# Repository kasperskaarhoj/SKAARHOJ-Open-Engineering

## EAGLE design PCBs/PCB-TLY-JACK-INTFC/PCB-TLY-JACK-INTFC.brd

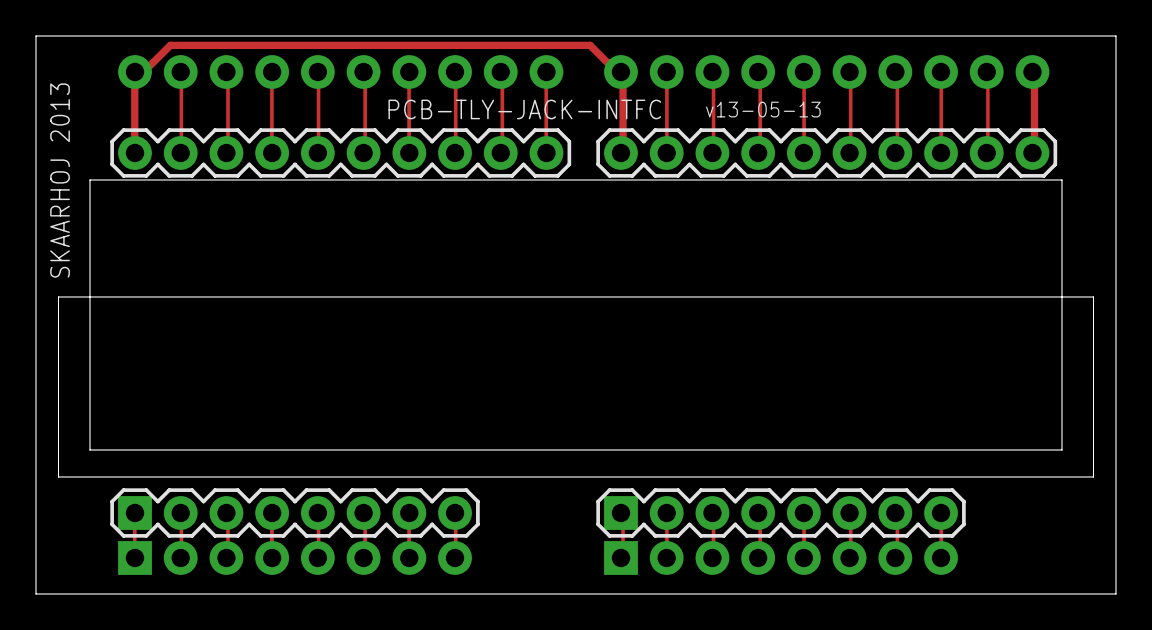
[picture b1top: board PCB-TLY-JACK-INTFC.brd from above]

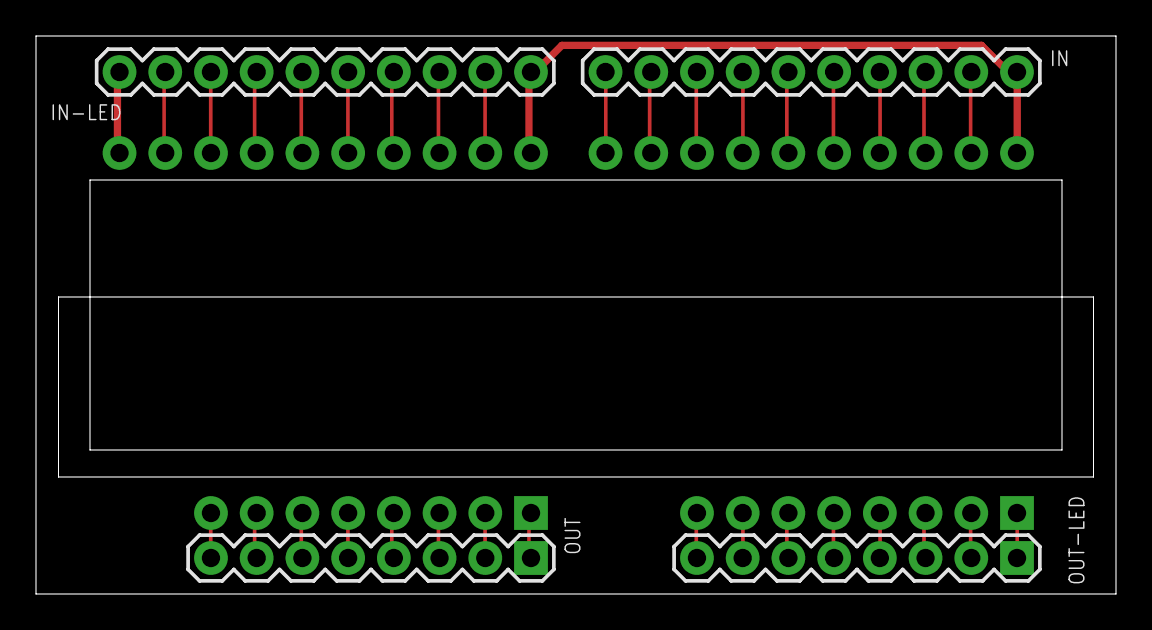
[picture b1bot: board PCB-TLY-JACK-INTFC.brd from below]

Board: 2 copper layers, 60.0 x 31.0 mm, 8 parts (4 on the bottom side), 35 nets.

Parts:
IN, IN1: M10"; 1X10
IN-LED, IN-LED1: M10"; 1X10
OUT, OUT1: 1X08
OUT-LED, OUT-LED1: 1X08

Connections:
5V: IN-LED.10, IN-LED1.10
GND: IN.1, IN1.1, IN-LED.1, IN-LED1.1
IN1: IN-LED.2, IN-LED1.2
IN2: IN-LED.3, IN-LED1.3
IN3: IN-LED.4, IN-LED1.4
IN4: IN-LED.5, IN-LED1.5
IN5: IN-LED.6, IN-LED1.6
IN6: IN-LED.7, IN-LED1.7
IN7: IN-LED.8, IN-LED1.8
IN8: IN-LED.9, IN-LED1.9
unnamed: IN.2, IN1.2
unnamed: IN.3, IN1.3
unnamed: IN.4, IN1.4
unnamed: IN.5, IN1.5
unnamed: IN.6, IN1.6
unnamed: IN.7, IN1.7
unnamed: IN.8, IN1.8
unnamed: IN.9, IN1.9
unnamed: IN.10, IN1.10
unnamed: OUT.8, OUT1.8
unnamed: OUT.7, OUT1.7
unnamed: OUT.6, OUT1.6
unnamed: OUT.5, OUT1.5
unnamed: OUT.4, OUT1.4
unnamed: OUT.3, OUT1.3
unnamed: OUT.2, OUT1.2
unnamed: OUT.1, OUT1.1
O1: OUT-LED.1, OUT-LED1.1
O2: OUT-LED.2, OUT-LED1.2
O3: OUT-LED.3, OUT-LED1.3
O4: OUT-LED.4, OUT-LED1.4
O5: OUT-LED.5, OUT-LED1.5
O6: OUT-LED.6, OUT-LED1.6
O7: OUT-LED.7, OUT-LED1.7
O8: OUT-LED.8, OUT-LED1.8

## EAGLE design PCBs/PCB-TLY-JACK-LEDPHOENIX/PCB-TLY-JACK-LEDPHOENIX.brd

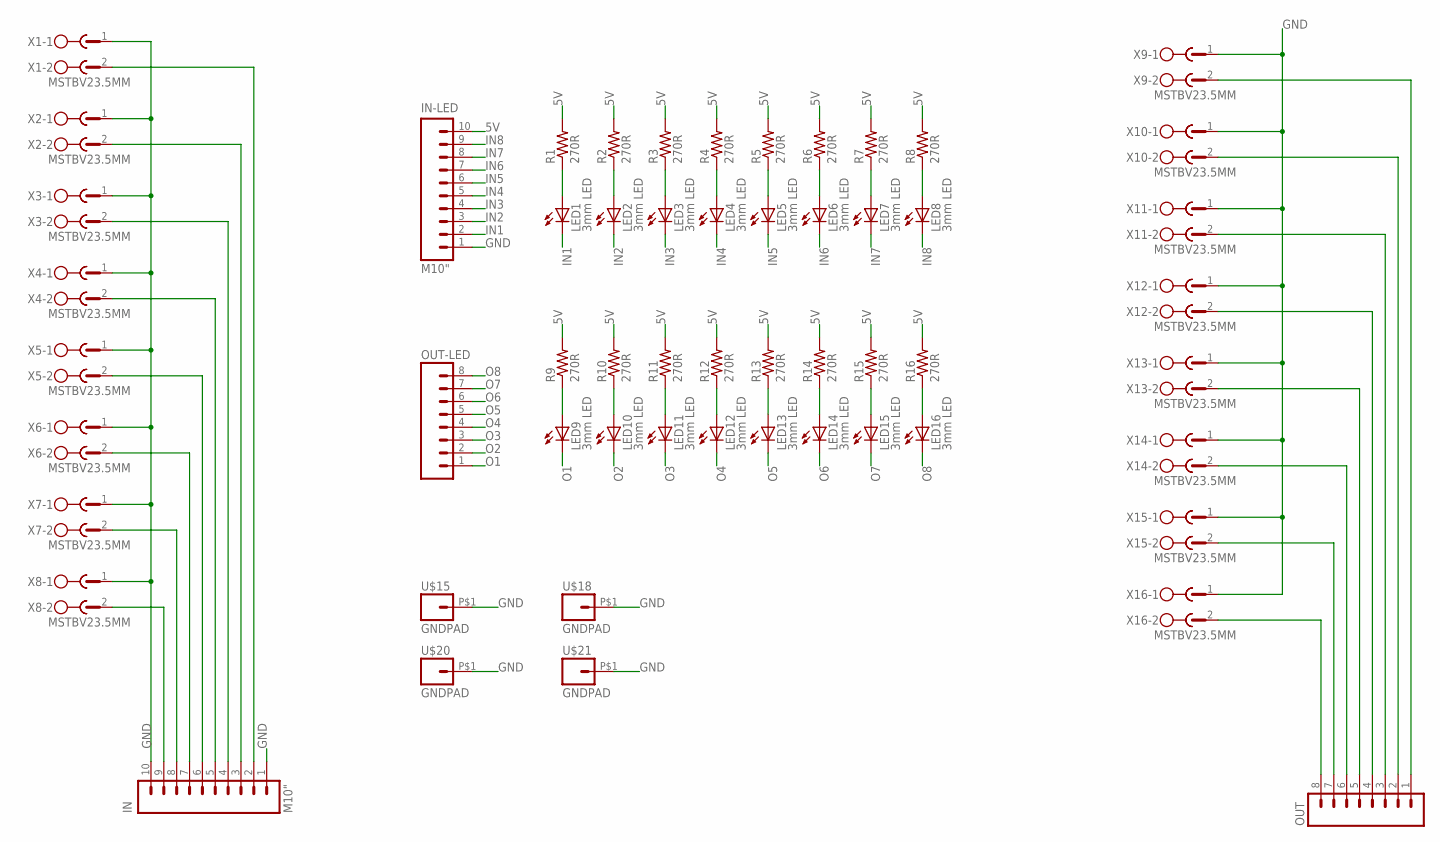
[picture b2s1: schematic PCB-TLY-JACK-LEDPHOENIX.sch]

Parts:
IN: M10"; 1X10
IN-LED: M10"; 1X10
LED1, LED2, LED3, LED4, LED5, LED6, LED7, LED8, LED9, LED10, LED11, LED12, LED13, LED14, LED15, LED16: 3mm LED; LED-1206
OUT: M081X08; 1X08
OUT-LED: M081X08; 1X08
R1, R2, R3, R4, R5, R6, R7, R8, R9, R10, R11, R12, R13, R14, R15, R16: 270R; 0603-RES
U$15, U$18, U$20, U$21: GNDPAD; 3.2MMPAD
X1, X2, X3, X4, X5, X6, X7, X8, X9, X10, X11, X12, X13, X14, X15, X16: MSTBV23.5MM; MSTBV2-3.5

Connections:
5V: IN-LED.10, R1.2, R2.2, R3.2, R4.2, R5.2, R6.2, R7.2, R8.2, R9.2, R10.2, R11.2, R12.2, R13.2, R14.2, R15.2, R16.2
GND: IN.1, IN.10, IN-LED.1, U$15.P$1, U$18.P$1, U$20.P$1, U$21.P$1, X1.1, X2.1, X3.1, X4.1, X5.1, X6.1, X7.1, X8.1, X9.1, X10.1, X11.1, X12.1, X13.1, X14.1, X15.1, X16.1
IN1: IN-LED.2, LED1.C
IN2: IN-LED.3, LED2.C
IN3: IN-LED.4, LED3.C
IN4: IN-LED.5, LED4.C
IN5: IN-LED.6, LED5.C
IN6: IN-LED.7, LED6.C
IN7: IN-LED.8, LED7.C
IN8: IN-LED.9, LED8.C
unnamed: LED1.A, R1.1
unnamed: LED2.A, R2.1
unnamed: LED3.A, R3.1
unnamed: LED4.A, R4.1
unnamed: LED5.A, R5.1
unnamed: LED6.A, R6.1
unnamed: LED7.A, R7.1
unnamed: LED8.A, R8.1
unnamed: LED9.A, R9.1
unnamed: LED10.A, R10.1
unnamed: LED11.A, R11.1
unnamed: LED12.A, R12.1
unnamed: LED13.A, R13.1
unnamed: LED14.A, R14.1
unnamed: LED15.A, R15.1
unnamed: LED16.A, R16.1
unnamed: OUT.2, X10.2
unnamed: OUT.3, X11.2
unnamed: OUT.4, X12.2
unnamed: OUT.5, X13.2
unnamed: OUT.1, X9.2
unnamed: OUT.6, X14.2
unnamed: OUT.7, X15.2
unnamed: OUT.8, X16.2
unnamed: IN.2, X1.2
unnamed: IN.6, X5.2
unnamed: IN.3, X2.2
unnamed: IN.4, X3.2
unnamed: IN.5, X4.2
unnamed: IN.7, X6.2
unnamed: IN.8, X7.2
unnamed: IN.9, X8.2
O1: LED9.C, OUT-LED.1
O2: LED10.C, OUT-LED.2
O3: LED11.C, OUT-LED.3
O4: LED12.C, OUT-LED.4
O5: LED13.C, OUT-LED.5
O6: LED14.C, OUT-LED.6
O7: LED15.C, OUT-LED.7
O8: LED16.C, OUT-LED.8

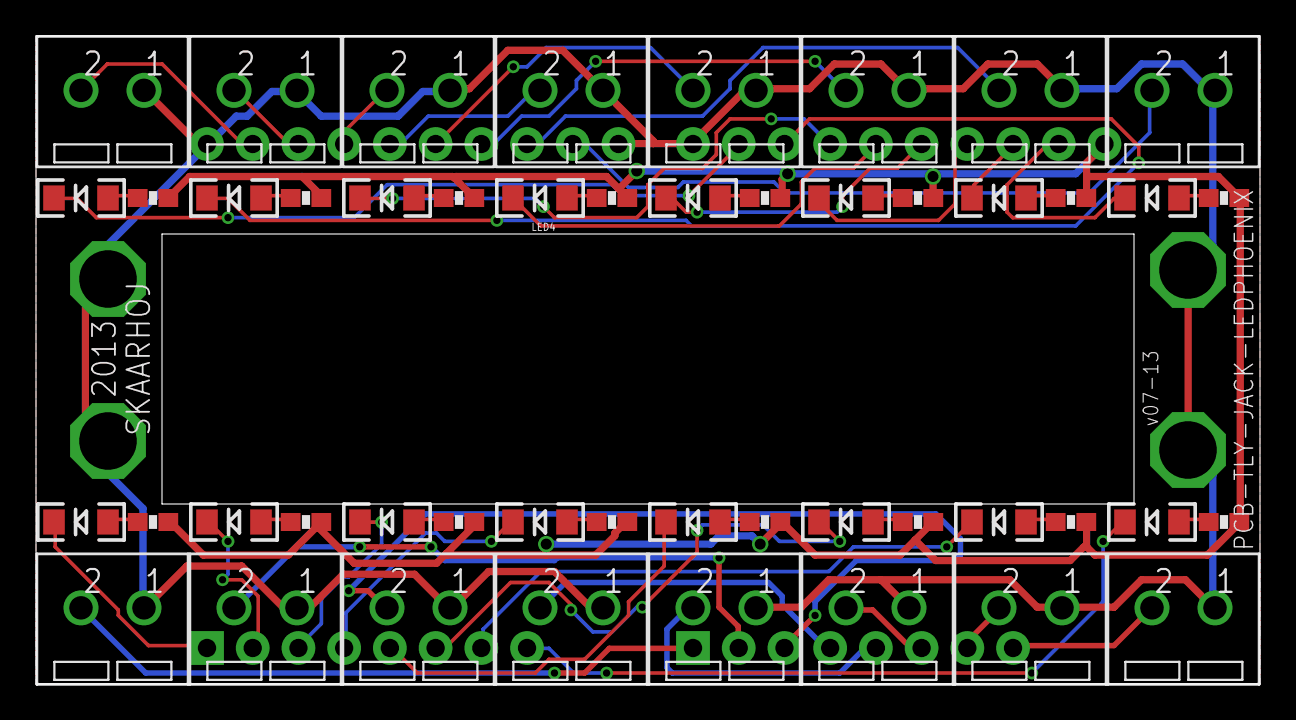
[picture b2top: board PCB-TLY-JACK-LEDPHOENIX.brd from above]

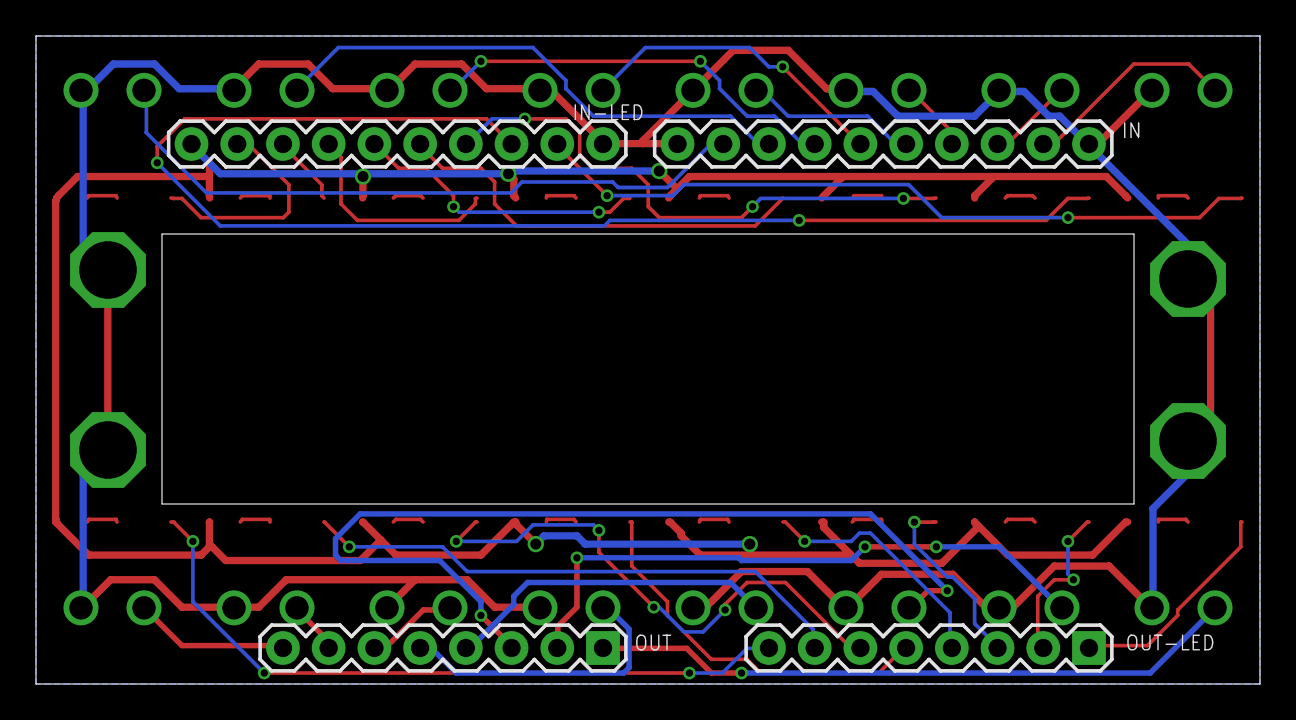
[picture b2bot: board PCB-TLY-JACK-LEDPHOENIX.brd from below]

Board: 2 copper layers, 68.0 x 36.0 mm, 56 parts (4 on the bottom side), 50 nets.

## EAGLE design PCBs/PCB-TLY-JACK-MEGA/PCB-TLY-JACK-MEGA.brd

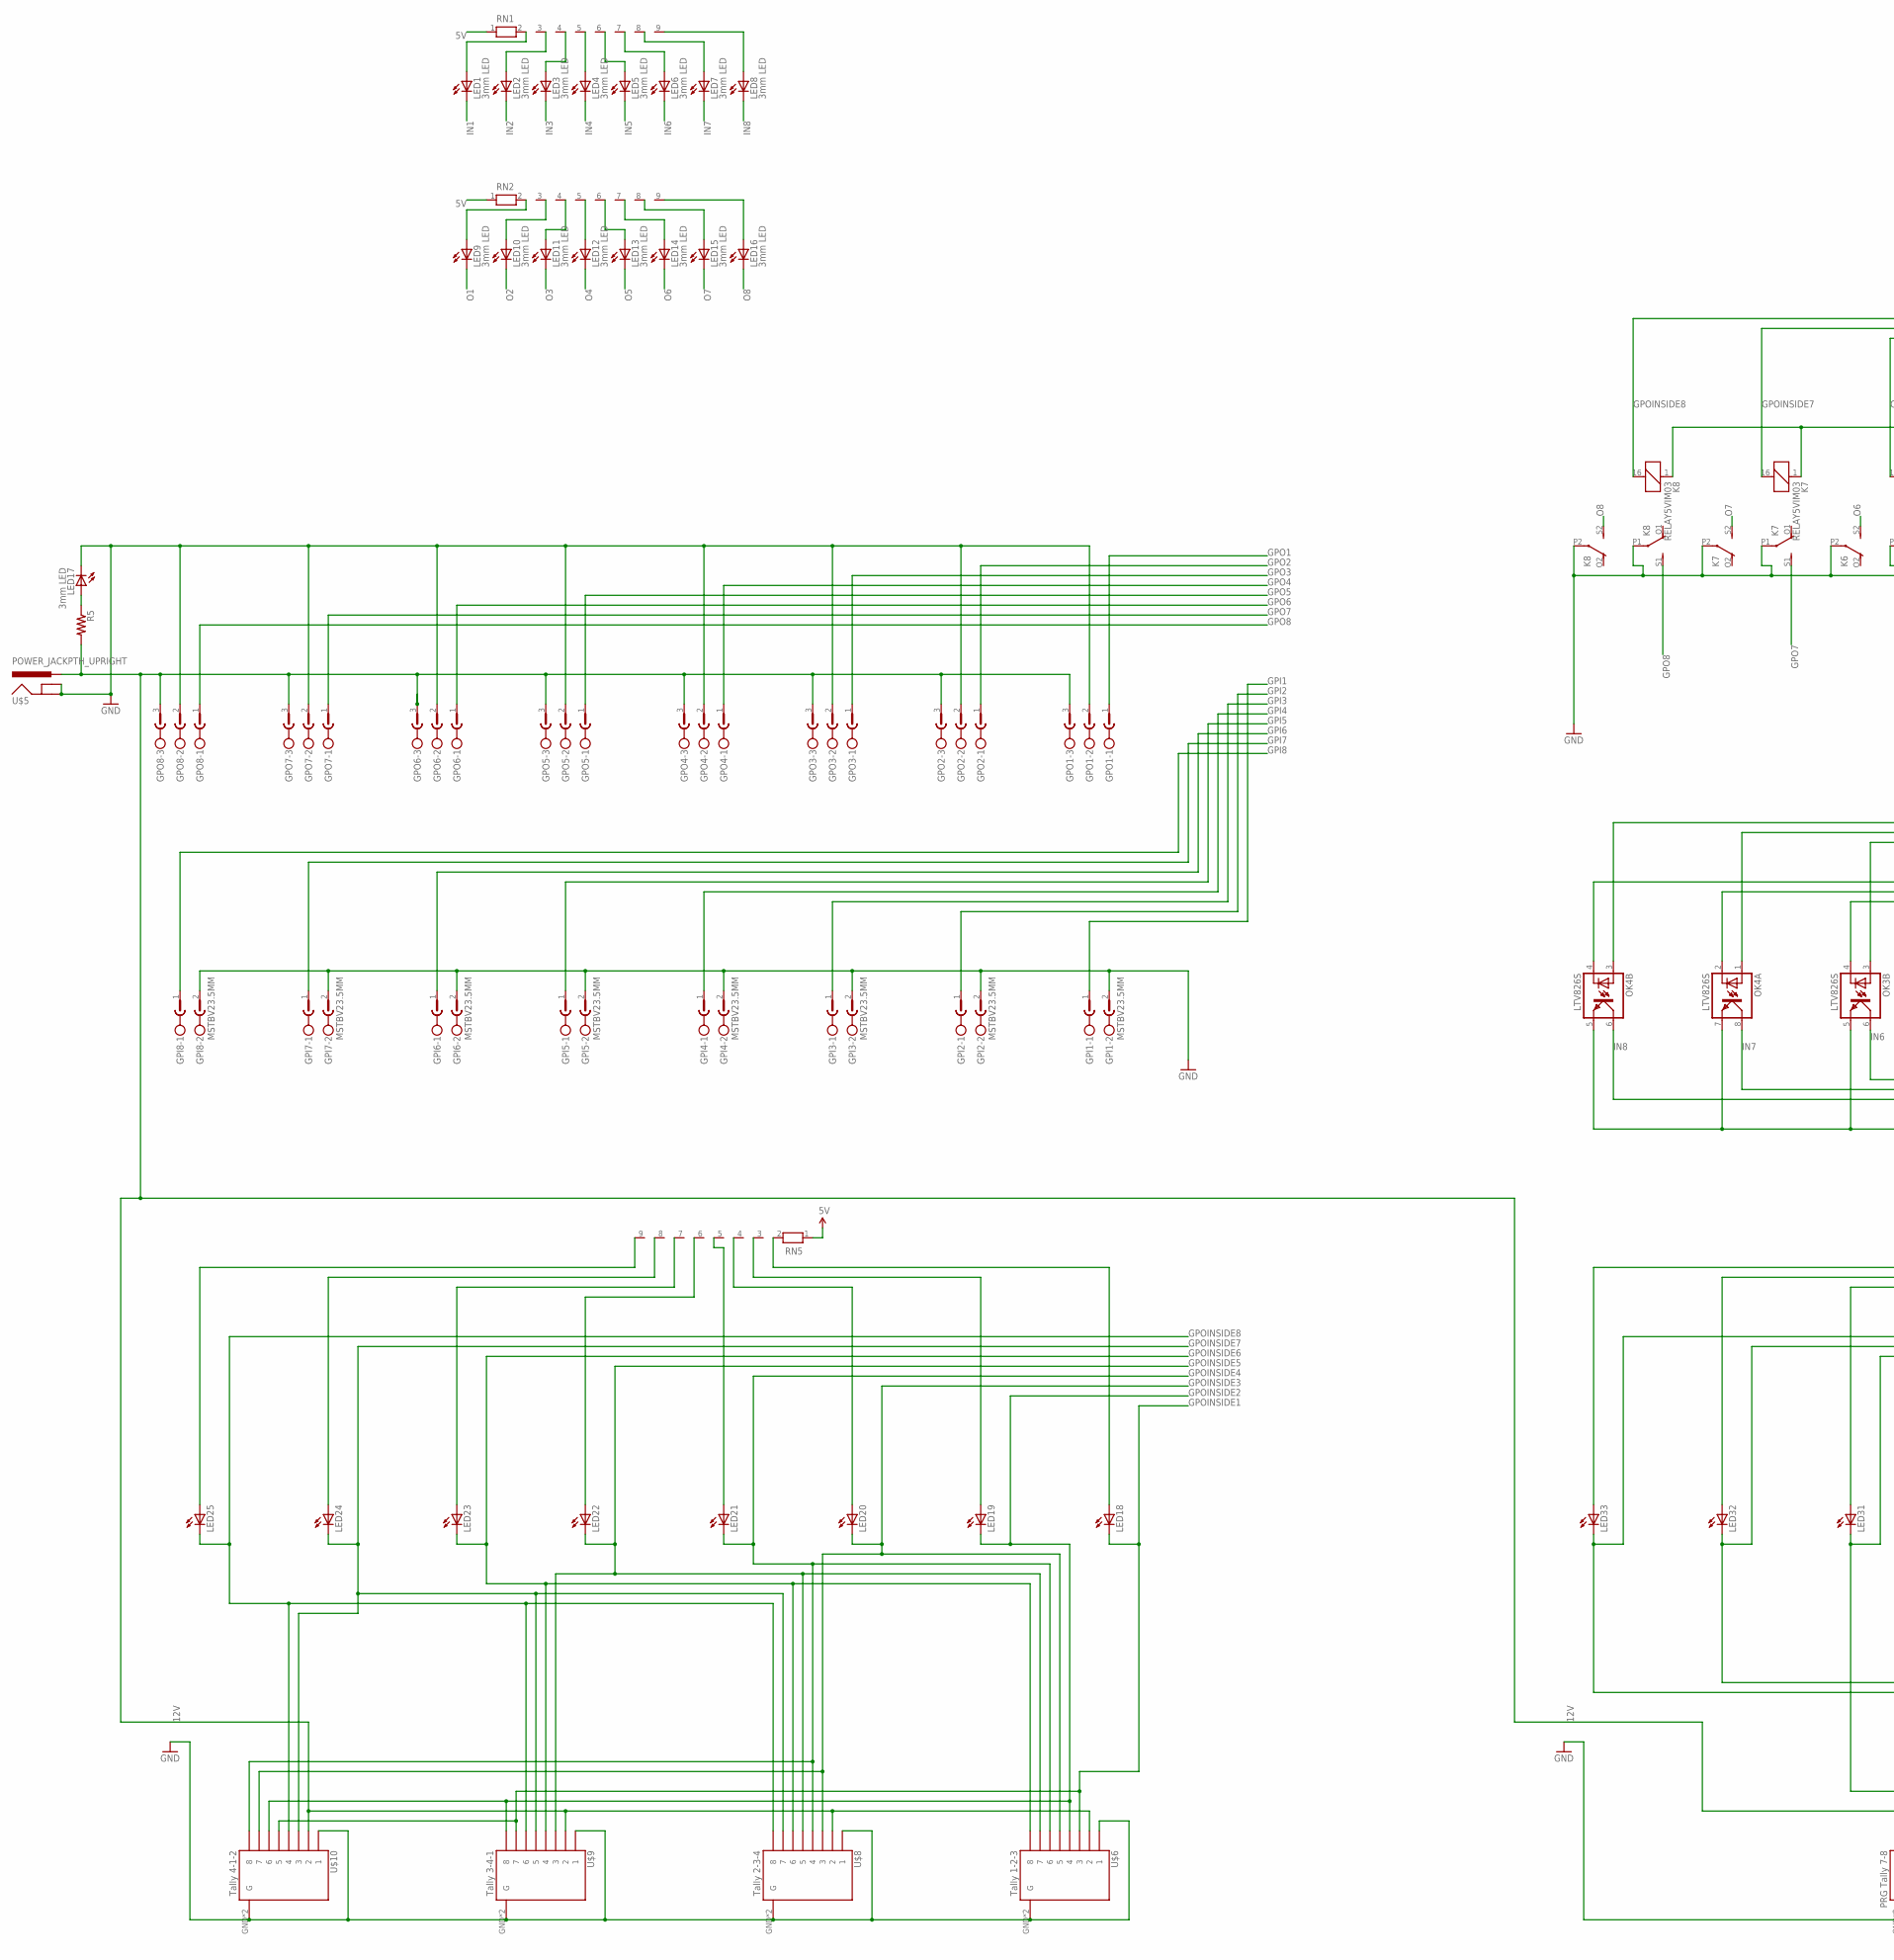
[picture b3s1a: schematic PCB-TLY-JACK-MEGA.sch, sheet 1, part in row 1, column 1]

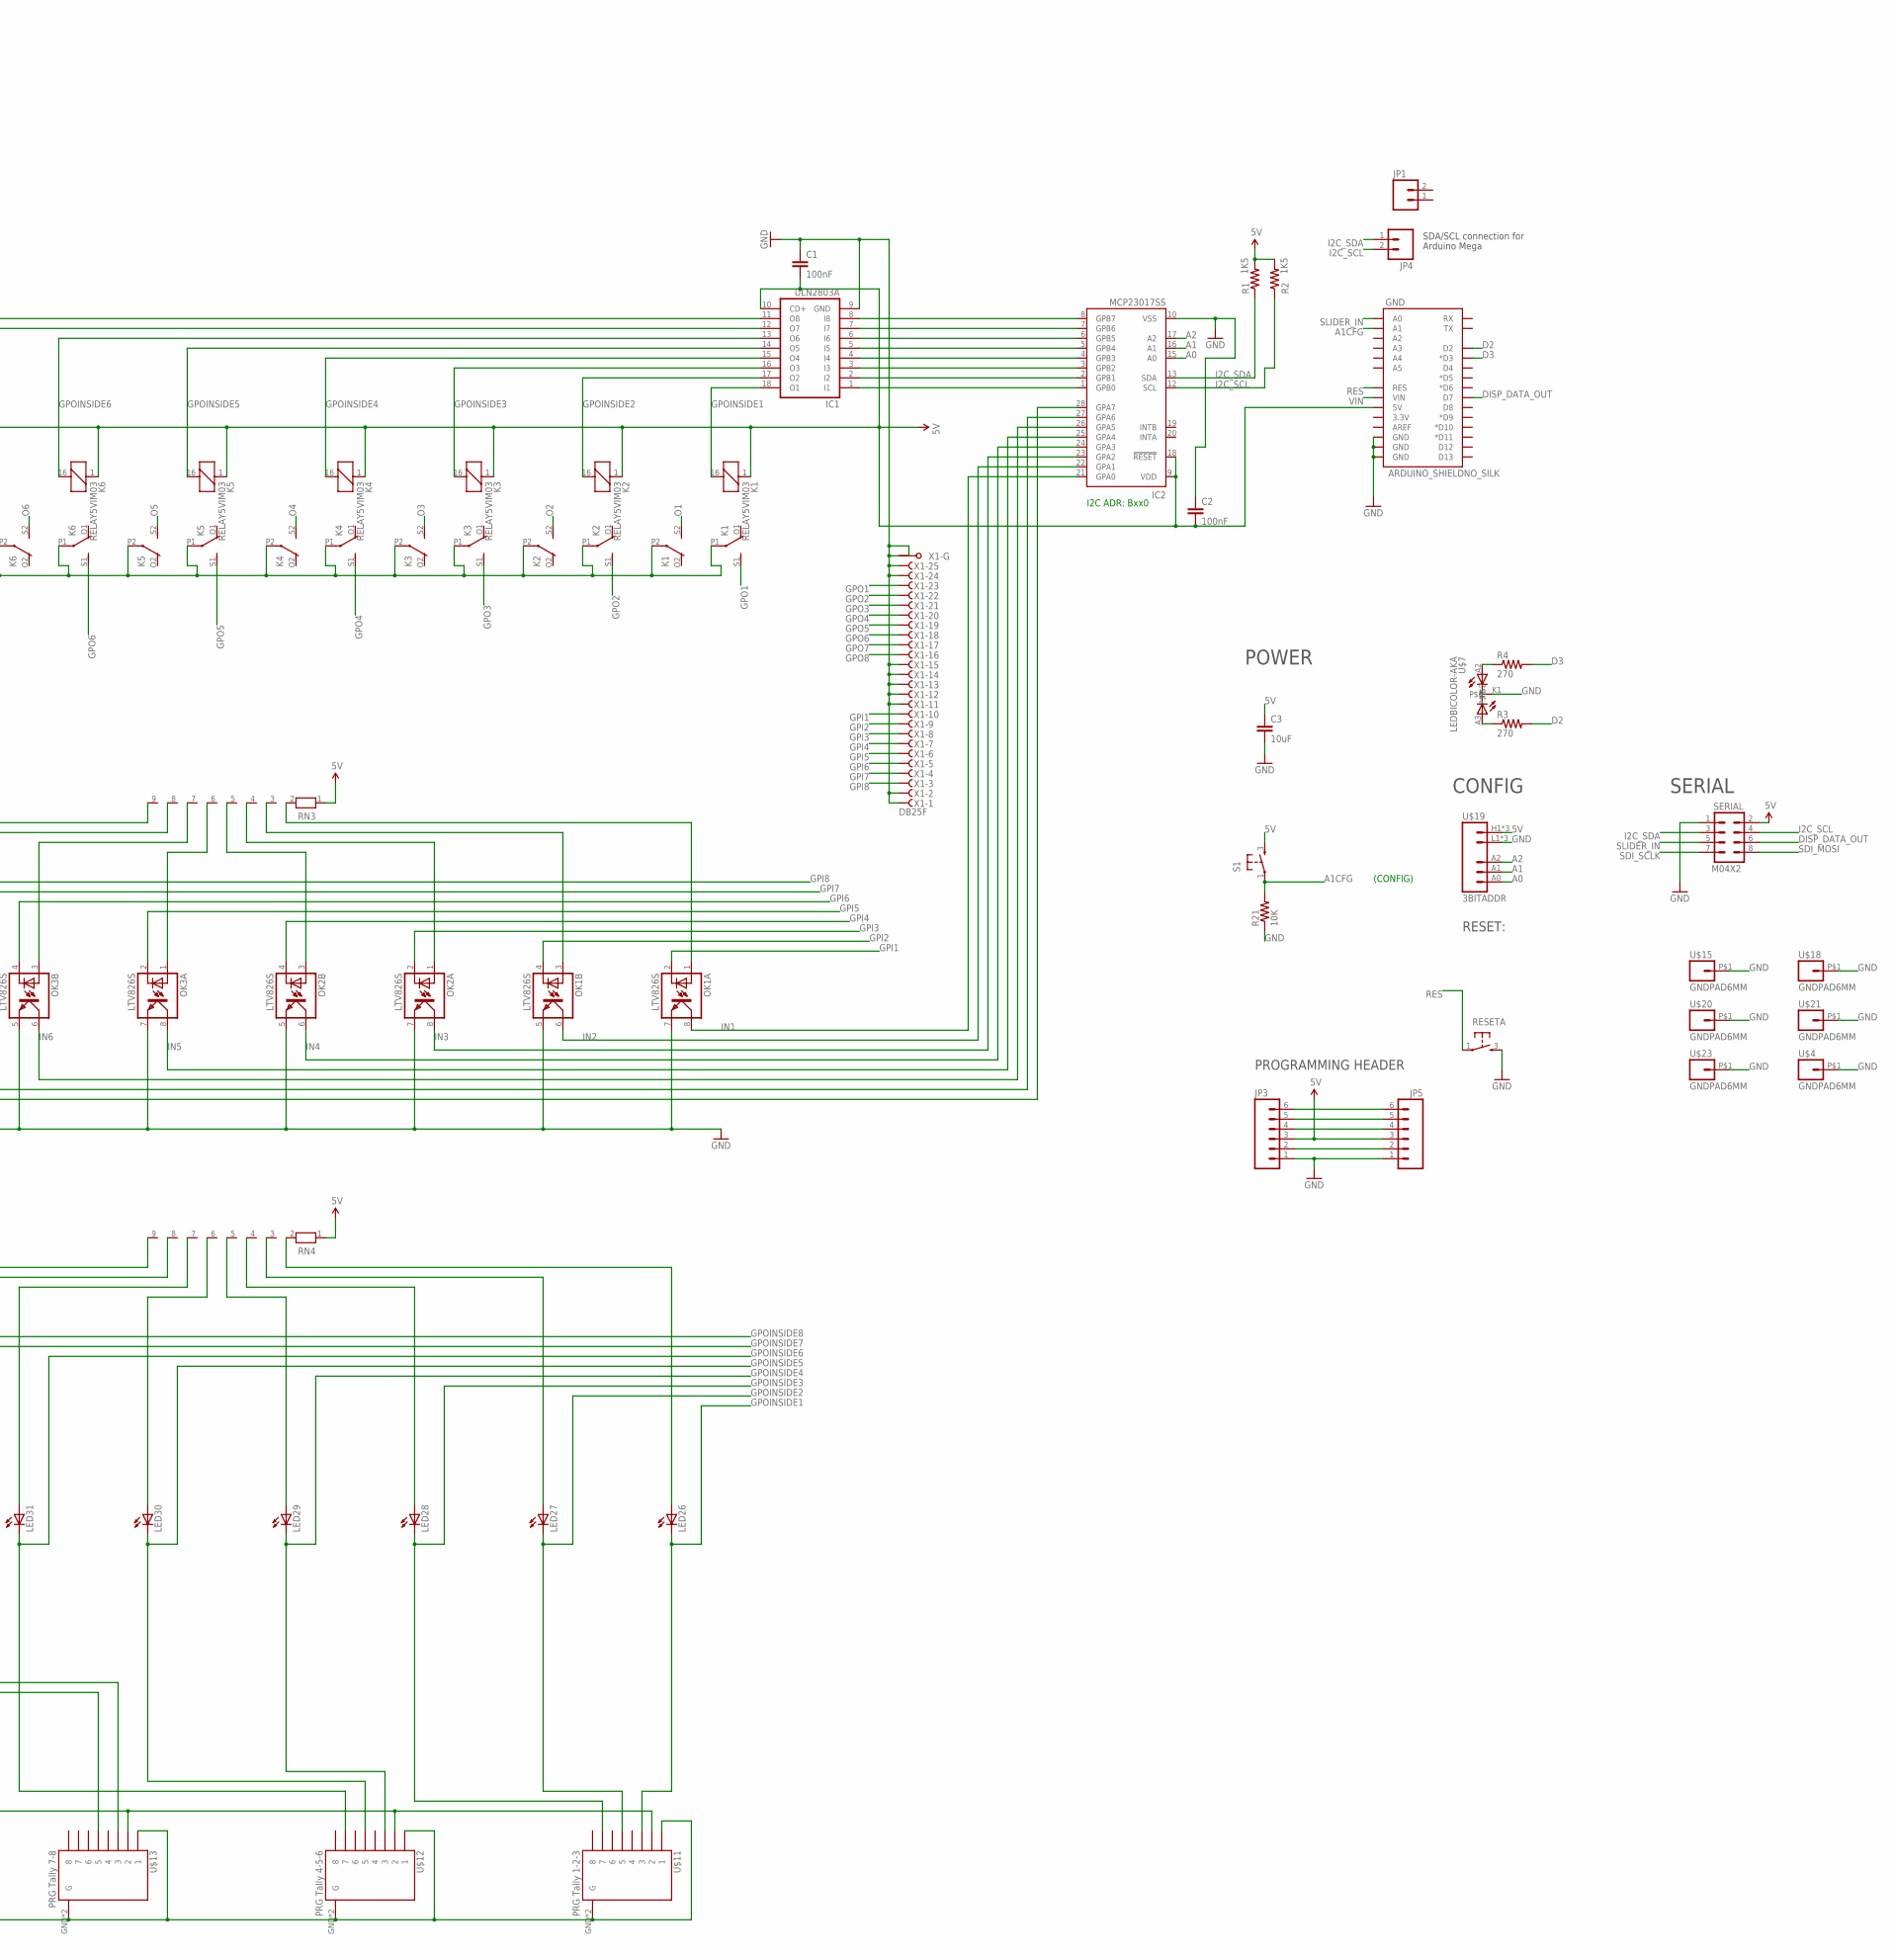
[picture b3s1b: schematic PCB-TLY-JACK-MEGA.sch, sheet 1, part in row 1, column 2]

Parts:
C1: 100nF; 0805
C2: 100nF; 0603-CAP
C3: 10uF; 0805
GND: ARDUINO_SHIELDNO_SILK; DUEMILANOVE_VIAS
GPI1, GPI2, GPI3, GPI4, GPI5, GPI6, GPI7, GPI8: MSTBV23.5MM; MSTBV2-3.5
GPO1, GPO2, GPO3, GPO4, GPO5, GPO6, GPO7, GPO8: CON1; MSTBV3-3.5
IC1: ULN2803A; SO18W
IC2: MCP23017SS; SSOP28
JP1, JP4: M02PTH; 1X02
JP3, JP5: M06POLAR; MOLEX-1X6
K1, K2, K3, K4, K5, K6, K7, K8: RELAY5VIM03; DS2Y
LED1, LED2, LED3, LED4, LED5, LED6, LED7, LED8, LED9, LED10, LED11, LED12, LED13, LED14, LED15, LED16, LED17: 3mm LED; LED3MM
LED18, LED19, LED20, LED21, LED22, LED23, LED24, LED25, LED26, LED27, LED28, LED29, LED30, LED31, LED32, LED33: LED3MM
OK1, OK2, OK3, OK4: LTV826S; DIL8-SMD
R1, R2: 1K5; 0603-RES
R3, R4: 270; 0603-RES
R5: RESISTOR0603-RES; 0603-RES
R21: 10K; 0603-RES
RESETA: TAC_SWITCH; PUSHBUTTON
RN1, RN2, RN3, RN4, RN5: RN08; RN-9
S1: TAC_SWITCH; PUSHBUTTON
SERIAL: M04X2; 2X4
U$4, U$15, U$18, U$20, U$21, U$23: GNDPAD6MM; 3.2MMPAD6MM
U$5: POWER_JACKPTH_UPRIGHT; POWER_JACK_PTH_UPRIGHT
U$6: Tally 1-2-3; RJ45-8_GND_UPRIGHT
U$7: LEDBICOLOR-AKA; LED5MM-BICOLOR
U$8: Tally 2-3-4; RJ45-8_GND_UPRIGHT
U$9: Tally 3-4-1; RJ45-8_GND_UPRIGHT
U$10: Tally 4-1-2; RJ45-8_GND_UPRIGHT
U$11: PRG Tally 1-2-3; RJ45-8_GND_UPRIGHT
U$12: PRG Tally 4-5-6; RJ45-8_GND_UPRIGHT
U$13: PRG Tally 7-8; RJ45-8_GND_UPRIGHT
U$19: 3BITADDR
X1: DB25F; F25HP

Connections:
5V: C1.2, C2.2, C3.1, GND.5V, IC1.10 (CD+), IC2.9 (VDD), IC2.18 (!RESET), JP3.3, JP5.3, K1.1, K2.1, K3.1, K4.1, K5.1, K6.1, K7.1, K8.1, R1.2, R2.2, RN1.1, RN2.1, RN3.1, RN4.1, RN5.1, S1.3, SERIAL.2, U$19.H1 (VCC), U$19.H2 (VCC), U$19.H3 (VCC)
12V: GPO1.3, GPO2.3, GPO3.3, GPO4.3, GPO5.3, GPO6.3, GPO7.3, GPO8.3, R5.2, U$5.PWR, U$6.2, U$8.2, U$9.2, U$10.2, U$11.2, U$12.2, U$13.2
A0: IC2.15 (A0), U$19.A0
A1: IC2.16 (A1), U$19.A1
A1CFG: GND.A1, R21.2, S1.1
A2: IC2.17 (A2), U$19.A2
D2: GND.D2, R3.2
D3: GND.D3 (*D3), R4.2
DISP_DATA_OUT: GND.D7, SERIAL.6
GND: C1.1, C2.1, C3.2, GND.GND@0 (GND), GND.GND@1 (GND), GND.GND@2 (GND), GPI1.2, GPI2.2, GPI3.2, GPI4.2, GPI5.2, GPI6.2, GPI7.2, GPI8.2, GPO1.2, GPO2.2, GPO3.2, GPO4.2, GPO5.2, GPO6.2, GPO7.2, GPO8.2, IC1.9 (GND), IC2.10 (VSS), JP3.1, JP5.1, K1.P1, K1.P2, K2.P1, K2.P2, K3.P1, K3.P2, K4.P1, K4.P2, K5.P1, K5.P2, K6.P1, K6.P2, K7.P1, K7.P2, K8.P1, K8.P2, LED17.K (C), OK1.5 (EMIT), OK1.7 (EMIT), OK2.5 (EMIT), OK2.7 (EMIT), OK3.5 (EMIT), OK3.7 (EMIT), OK4.5 (EMIT), OK4.7 (EMIT), R21.1, RESETA.3, SERIAL.1, U$4.P$1, U$5.GND, U$5.SHUNT (GNDBREAK), U$6.1, U$6.GND (G), U$6.GND1 (G), U$7.K1, U$8.1, U$8.GND (G), U$8.GND1 (G), U$9.1, U$9.GND (G), U$9.GND1 (G), U$10.1, U$10.GND (G), U$10.GND1 (G), U$11.1, U$11.GND (G), U$11.GND1 (G), U$12.1, U$12.GND (G), U$12.GND1 (G), U$13.1, U$13.GND (G), U$13.GND1 (G), U$15.P$1, U$18.P$1, U$19.L1 (GND), U$19.L2 (GND), U$19.L3 (GND), U$20.P$1, U$21.P$1, U$23.P$1, X1.1 (F), X1.2 (F), X1.11 (F), X1.12 (F), X1.13 (F), X1.14 (F), X1.15 (F), X1.24 (F), X1.25 (F), X1.G1, X1.G2
GPI1: GPI1.1, OK1.2 (C), X1.10 (F)
GPI2: GPI2.1, OK1.4 (C), X1.9 (F)
GPI3: GPI3.1, OK2.2 (C), X1.8 (F)
GPI4: GPI4.1, OK2.4 (C), X1.7 (F)
GPI5: GPI5.1, OK3.2 (C), X1.6 (F)
GPI6: GPI6.1, OK3.4 (C), X1.5 (F)
GPI7: GPI7.1, OK4.2 (C), X1.4 (F)
GPI8: GPI8.1, OK4.4 (C), X1.3 (F)
GPO1: GPO1.1, K1.S1 (S), X1.23 (F)
GPO2: GPO2.1, K2.S1 (S), X1.22 (F)
GPO3: GPO3.1, K3.S1 (S), X1.21 (F)
GPO4: GPO4.1, K4.S1 (S), X1.20 (F)
GPO5: GPO5.1, K5.S1 (S), X1.19 (F)
GPO6: GPO6.1, K6.S1 (S), X1.18 (F)
GPO7: GPO7.1, K7.S1 (S), X1.17 (F)
GPO8: GPO8.1, K8.S1 (S), X1.16 (F)
GPOINSIDE1: IC1.18 (O1), K1.16 (2), LED18.K (C), LED26.K (C), U$6.3, U$9.7, U$10.5, U$11.3
GPOINSIDE2: IC1.17 (O2), K2.16 (2), LED19.K (C), LED27.K (C), U$6.4, U$9.8, U$10.6, U$11.5
GPOINSIDE3: IC1.16 (O3), K3.16 (2), LED20.K (C), LED28.K (C), U$6.5, U$8.3, U$10.7, U$11.7
GPOINSIDE4: IC1.15 (O4), K4.16 (2), LED21.K (C), LED29.K (C), U$6.6, U$8.4, U$10.8, U$12.3
GPOINSIDE5: IC1.14 (O5), K5.16 (2), LED22.K (C), LED30.K (C), U$6.7, U$8.5, U$9.3, U$12.5
GPOINSIDE6: IC1.13 (O6), K6.16 (2), LED23.K (C), LED31.K (C), U$6.8, U$8.6, U$9.4, U$12.7
GPOINSIDE7: IC1.12 (O7), K7.16 (2), LED24.K (C), LED32.K (C), U$8.7, U$9.5, U$10.3, U$13.3
GPOINSIDE8: IC1.11 (O8), K8.16 (2), LED25.K (C), LED33.K (C), U$8.8, U$9.6, U$10.4, U$13.5
I2C_SCL: IC2.12 (SCL), JP4.2, R2.1, SERIAL.4
I2C_SDA: IC2.13 (SDA), JP4.1, R1.1, SERIAL.3
IN1: IC2.21 (GPA0), LED1.K (C), OK1.8 (COL)
IN2: IC2.22 (GPA1), LED2.K (C), OK1.6 (COL)
IN3: IC2.23 (GPA2), LED3.K (C), OK2.8 (COL)
IN4: IC2.24 (GPA3), LED4.K (C), OK2.6 (COL)
IN5: IC2.25 (GPA4), LED5.K (C), OK3.8 (COL)
IN6: IC2.26 (GPA5), LED6.K (C), OK3.6 (COL)
IN7: IC2.27 (GPA6), LED7.K (C), OK4.8 (COL)
IN8: IC2.28 (GPA7), LED8.K (C), OK4.6 (COL)
unnamed: LED1.A, RN1.2
unnamed: LED2.A, RN1.3
unnamed: JP3.4, JP5.4
unnamed: LED18.A, RN5.2
unnamed: IC1.1 (I1), IC2.1 (GPB0)
unnamed: LED3.A, RN1.4
unnamed: R4.1, U$7.A2
unnamed: JP3.5, JP5.5
unnamed: LED19.A, RN5.3
unnamed: LED4.A, RN1.5
unnamed: R3.1, U$7.A3
unnamed: JP3.2, JP5.2
unnamed: LED20.A, RN5.4
unnamed: LED5.A, RN1.6
unnamed: LED6.A, RN1.7
unnamed: LED7.A, RN1.8
unnamed: LED21.A, RN5.5
unnamed: LED8.A, RN1.9
unnamed: LED9.A, RN2.2
unnamed: LED10.A, RN2.3
unnamed: LED22.A, RN5.6
unnamed: LED11.A, RN2.4
unnamed: LED12.A, RN2.5
unnamed: LED13.A, RN2.6
unnamed: LED23.A, RN5.7
unnamed: LED14.A, RN2.7
unnamed: LED15.A, RN2.8
unnamed: LED16.A, RN2.9
unnamed: LED24.A, RN5.8
unnamed: LED17.A, R5.1
unnamed: LED25.A, RN5.9
unnamed: LED26.A, RN4.2
unnamed: LED27.A, RN4.3
unnamed: IC1.2 (I2), IC2.2 (GPB1)
unnamed: IC1.3 (I3), IC2.3 (GPB2)
unnamed: IC1.4 (I4), IC2.4 (GPB3)
unnamed: IC1.5 (I5), IC2.5 (GPB4)
unnamed: IC1.6 (I6), IC2.6 (GPB5)
unnamed: IC1.7 (I7), IC2.7 (GPB6)
unnamed: IC1.8 (I8), IC2.8 (GPB7)
unnamed: LED28.A, RN4.4
unnamed: LED29.A, RN4.5
unnamed: LED30.A, RN4.6
unnamed: LED31.A, RN4.7
unnamed: JP3.6, JP5.6
unnamed: LED32.A, RN4.8
unnamed: LED33.A, RN4.9
unnamed: OK1.1 (A), RN3.2
unnamed: OK1.3 (A), RN3.3
unnamed: OK2.1 (A), RN3.4
unnamed: OK2.3 (A), RN3.5
unnamed: OK3.1 (A), RN3.6
unnamed: OK3.3 (A), RN3.7
unnamed: OK4.1 (A), RN3.8
unnamed: OK4.3 (A), RN3.9
O1: K1.S2 (S), LED9.K (C)
O2: K2.S2 (S), LED10.K (C)
O3: K3.S2 (S), LED11.K (C)
O4: K4.S2 (S), LED12.K (C)
O5: K5.S2 (S), LED13.K (C)
O6: K6.S2 (S), LED14.K (C)
O7: K7.S2 (S), LED15.K (C)
O8: K8.S2 (S), LED16.K (C)
RES: GND.RES, RESETA.1
SDI_MOSI: SERIAL.8
SDI_SCLK: SERIAL.7
SLIDER_IN: GND.A0, SERIAL.5
VIN: GND.VIN

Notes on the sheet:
I2C ADR: Bxx0
SDA/SCL connection for
Arduino Mega
POWER
(CONFIG)
SERIAL
CONFIG
RESET:
PROGRAMMING HEADER

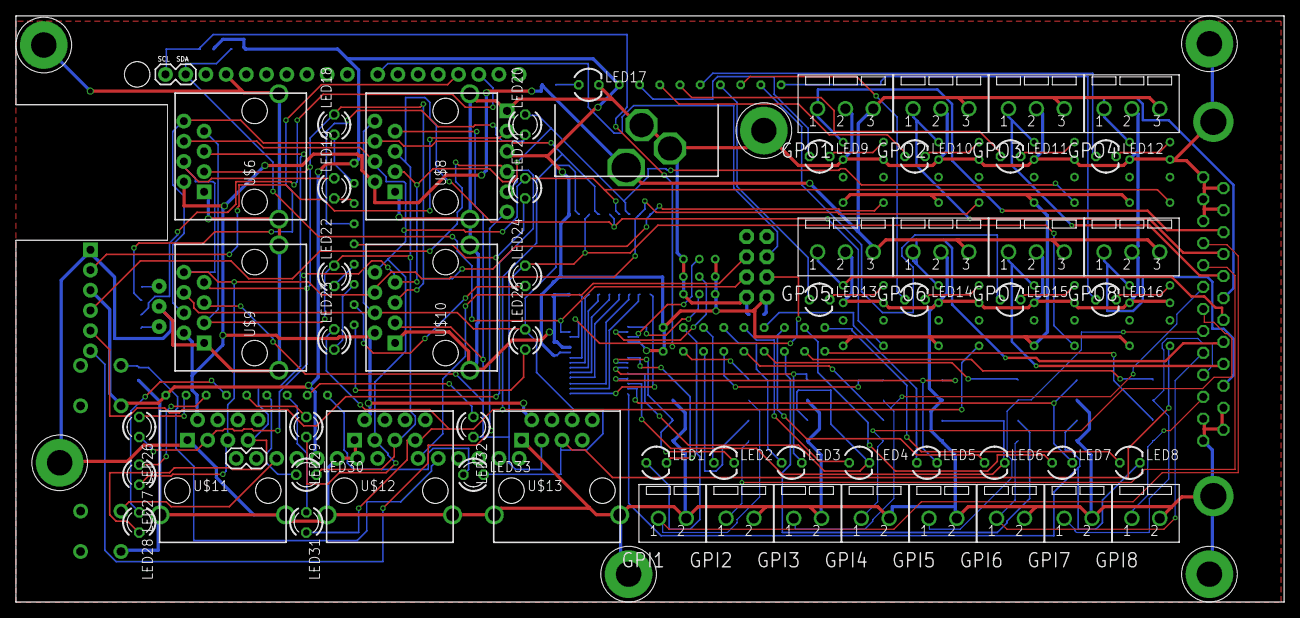
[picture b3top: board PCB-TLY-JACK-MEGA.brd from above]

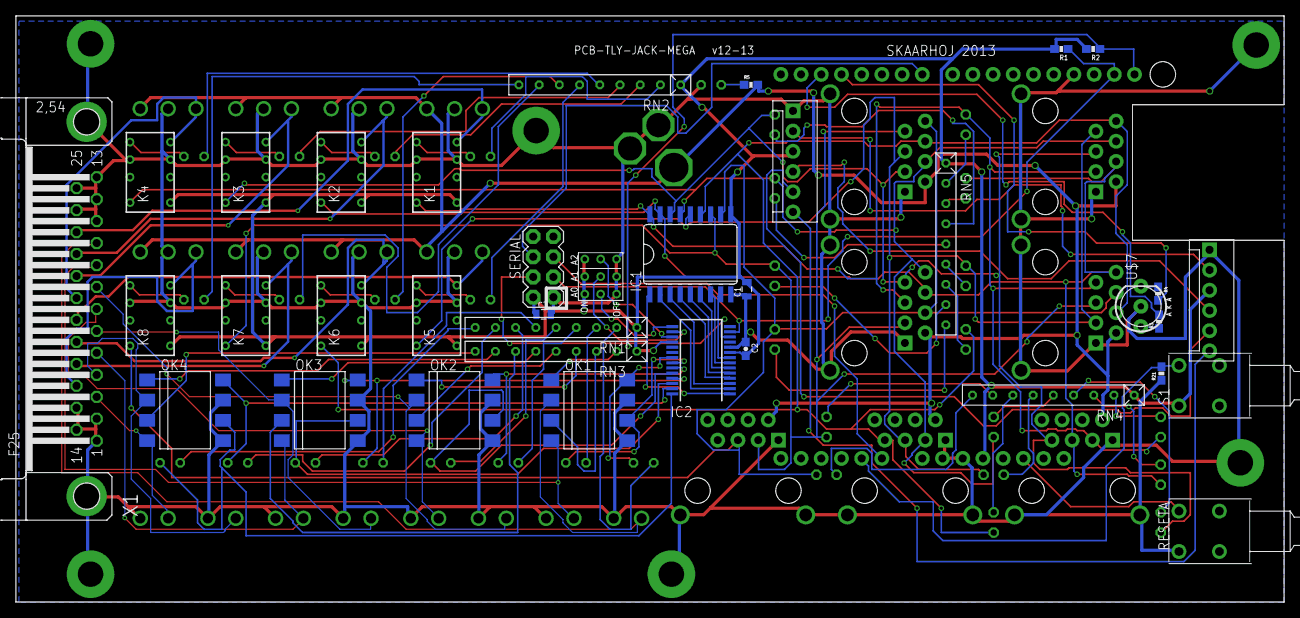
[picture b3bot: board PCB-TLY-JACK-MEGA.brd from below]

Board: 2 copper layers, 159.4 x 73.7 mm, 102 parts (36 on the bottom side), 109 nets.

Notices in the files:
parts and their libraries:
SparkFun: Licensing: CC v3.0 Share-Alike You are welcome to use this library for commercial purposes.
